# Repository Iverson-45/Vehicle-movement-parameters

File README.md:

Vehicle Movement Parameters Meter 
------

Authors: Jakub Litwin, Mateusz Prądziński, Adrian Andrószowski, Błażej Szkobel 
Overview

The goal of this project is to design and build a prototype device capable of measuring, calculating, and displaying real-time vehicle movement parameters. To ensure high data throughput, low latency, and a responsive UI, the system utilizes a Dual-MCU architecture that effectively splits the workload between sensor processing and data logging/display.
Calculated & Displayed Parameters:

    Speed: [km/h] 

    Acceleration: [m/s^2] (Instantaneous acceleration) 

    Power: [Hp] 

    Torque: [Nm] 

    Inclination: [°] (Pitch / Roll) 

Hardware Architecture

The device operates on two separate microcontrollers communicating via UART.

1. Main MCU (Data Processor)

    Microcontroller: STM32F411CEU6 

    Role: Handles all sensor data acquisition, scaling, filtration, and complex sensor fusion algorithms.

    Sensors: U-blox NEO-M8N (GPS) and BMI160 (IMU + Gyroscope).

2. Secondary MCU (Display & Logger)

    Microcontroller: STM32f303k8 

    Role: Receives processed numerical data from the Main MCU and handles the user interface.

    Peripherals: Drives a 2.0-inch TFT SPI Display and handles .csv data logging to a microSD card.

Firmware & Communication

    Main MCU: Programmed in low-level C (registers) to highly optimize the code for its specific tasks. It uses interrupt-driven peripherals to minimize delays and ensure smooth data reception. It synchronizes 100 data reads per second from the BMI160 and 5 reads per second from the GPS.

    Auxiliary MCU: Written in C utilizing the HAL library. It implements heavily optimized external libraries from GitHub for the ST7789 display and SPI SD card.

    Inter-MCU Communication: The two microcontrollers communicate via UART. At startup, they perform a handshake to initiate communication. The Aux MCU sends the user-defined vehicle mass to the Main MCU, and the Main MCU continuously streams back the calculated data.

How It Works: Algorithms & Calibration

To make the device user-friendly, it does not require perfectly leveled physical mounting inside the vehicle. Instead, the data passes through a complex algorithmic pipeline divided into three distinct phases:

Phase 1: Gravity Calibration While the vehicle is completely stationary, the device measures the Earth's gravitational pull to determine the gravity vector relative to the device's physical orientation. This establishes the true Z-axis (downward force).

Phase 2: Longitudinal Axis Calibration (Direction) The user performs a short, straight-line acceleration. The device detects this forward motion vector to define the X-axis (front). Using the cross product of these established forces, the software builds an orthonormal basis. This creates a 3D rotation matrix that mathematically rotates all raw sensor vectors to perfectly align with the vehicle's actual coordinate system, automatically compensating for any "crooked" mounting.

Phase 3: Active Operation During driving, raw data from the accelerometer and gyroscope is continuously transformed using the generated rotation matrix. The system calculates the device's tilt angles from the accelerometer and applies a Complementary Filter to fuse this data with the gyroscope readings for smooth, accurate inclination and acceleration outputs.
Current State & Future Development

Semester 1 Achievements:
A fully working prototype has been built that successfully handles instrument communication, calibration algorithms, the user interface, display presentation, and SD card .csv logging.

Next Steps (Semester 2 Goals): 

    Design a dedicated power supply section.

    Create a complete device schematic and custom PCB layout.

    Design a physical 3D enclosure/case.

    Conduct extensive real-world measurement tests.

    Develop PC software to visualize the saved telemetry data.

## Preliminary Measurement Results

During our initial field tests, the logged telemetry data was extracted and visualized using Python. We are pleased to report that the calculated power output closely aligns with the actual specifications of the vehicle used for testing.

**⚠️ Note:** Please keep in mind that this is an early prototype and not the final version of the system. The hardware architecture and calculation algorithms are still actively being refined. Further calibration, optimization, and extensive real-world validations are planned for the upcoming semester.

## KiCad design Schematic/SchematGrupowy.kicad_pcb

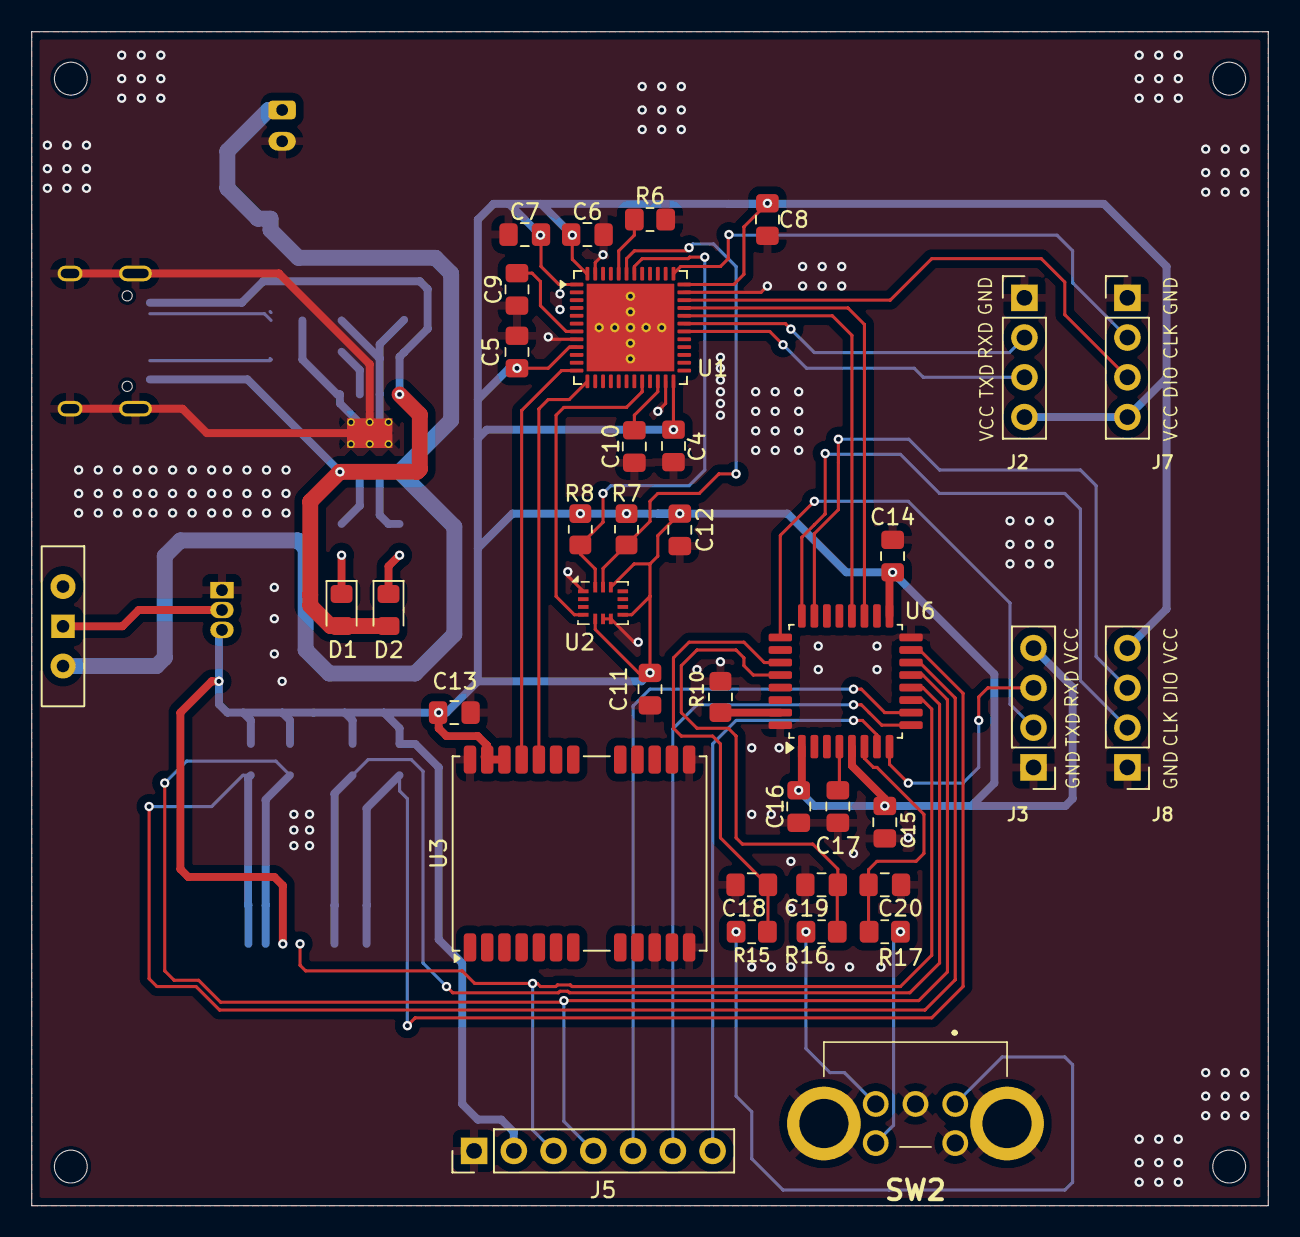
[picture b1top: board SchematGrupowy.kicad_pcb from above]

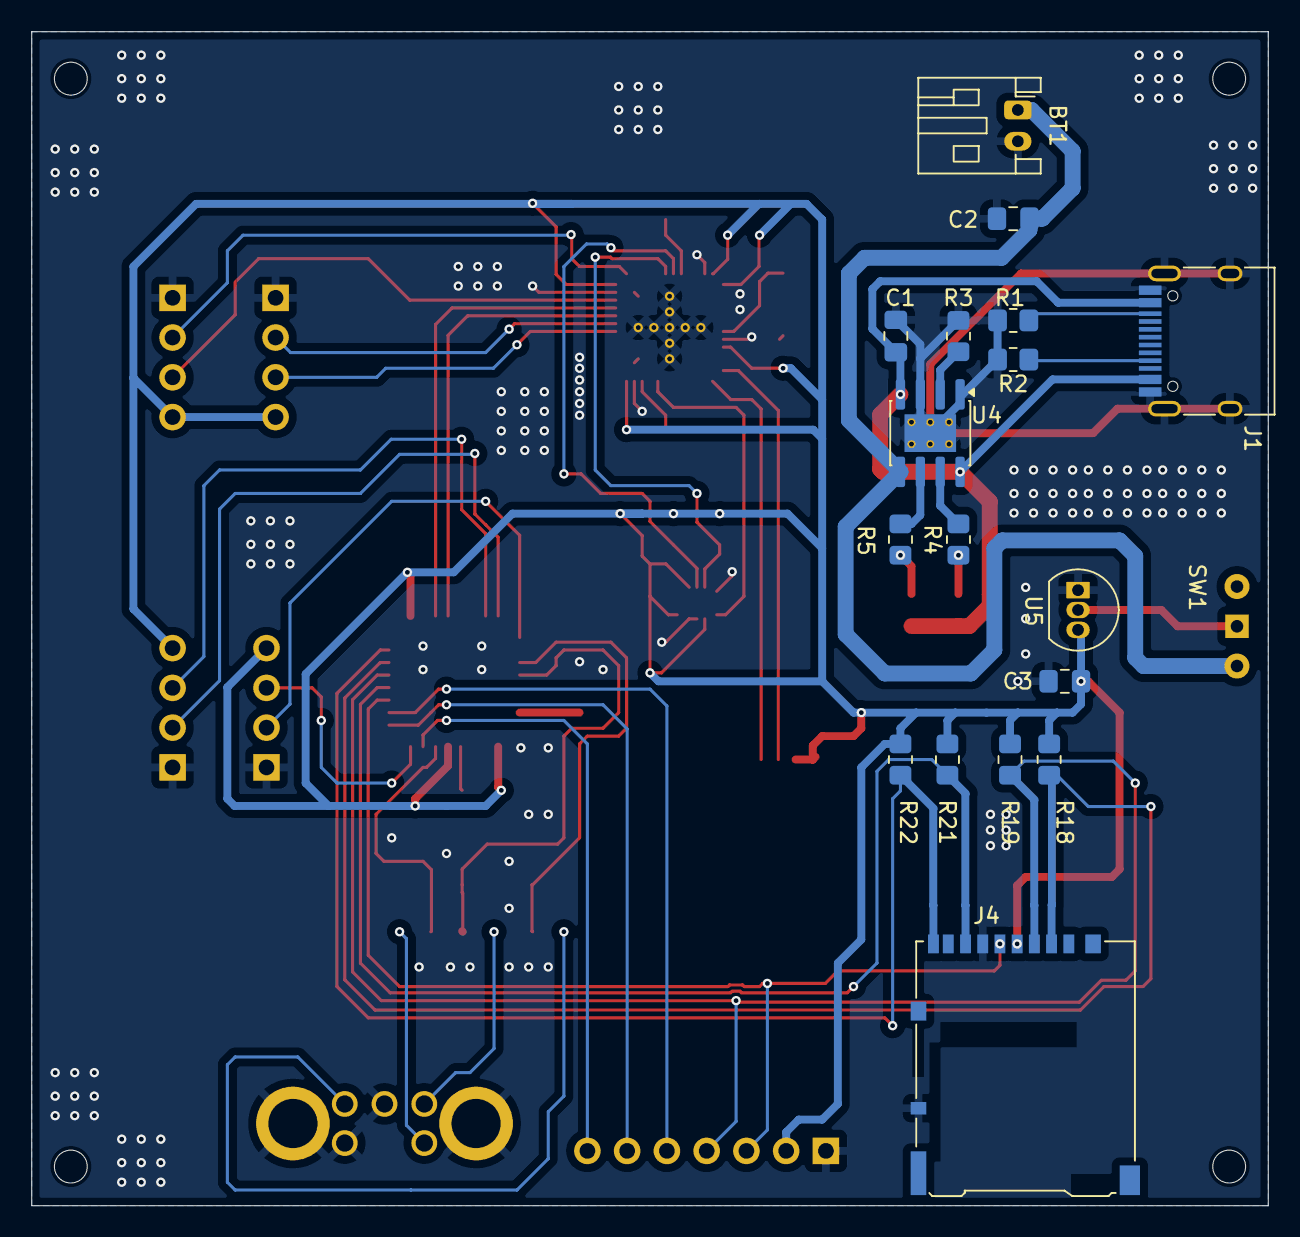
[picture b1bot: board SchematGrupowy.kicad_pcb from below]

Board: 2 copper layers, 79.0 x 75.0 mm, 54 parts (17 on the bottom side), 46 nets.

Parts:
BT1: Battery_Cell; JST_PH_S2B-PH-K_1x02_P2.00mm_Horizontal
C1, C2, C3: 10uF; C_0805_2012Metric_Pad1.18x1.45mm_HandSolder
C4: 4.7uF; C_0805_2012Metric_Pad1.18x1.45mm_HandSolder
C5, C6, C7, C8, C10, C11, C12, C13, C14, C15, C16: 100nF; C_0805_2012Metric_Pad1.18x1.45mm_HandSolder
C9, C17: 100n; C_0805_2012Metric_Pad1.18x1.45mm_HandSolder
C18, C19, C20: 10nF; C_0805_2012Metric_Pad1.18x1.45mm_HandSolder
D1, D2: LED; LED_0805_2012Metric_Pad1.15x1.40mm_HandSolder
J1: USB_C_Receptacle_USB2.0_14P; USB_C_Receptacle_HRO_TYPE-C-31-M-12
J2: UART1; PinHeader_1x04_P2.54mm_Vertical
J3: UART2; PinHeader_1x04_P2.54mm_Vertical
J4: Micro_SD_Card_Det1; microSD_HC_Hirose_DM3AT-SF-PEJM5
J5: LCD; PinHeader_1x07_P2.54mm_Vertical
J7: Programing1; PinHeader_1x04_P2.54mm_Vertical
J8: Programing2; PinHeader_1x04_P2.54mm_Vertical
R1, R2: 5.1k; R_0805_2012Metric_Pad1.20x1.40mm_HandSolder
R3: 1.1k; R_0805_2012Metric_Pad1.20x1.40mm_HandSolder
R4, R5: 1k; R_0805_2012Metric_Pad1.20x1.40mm_HandSolder
R6, R10, R15, R16, R17, R18, R19, R21, R22: 10k; R_0805_2012Metric_Pad1.20x1.40mm_HandSolder
R7, R8: 4.7k; R_0805_2012Metric_Pad1.20x1.40mm_HandSolder
SW1: SW_Wuerth_450301014042; SW_Slide-03_Wuerth-WS-SLTV_10x2.5x6.4_P2.54mm
SW2: RotaryEncoder_Switch_MP; EC11B15242AE
U1: STM32F411CEUx; QFN-48-1EP_7x7mm_P0.5mm_EP5.6x5.6mm
U2: BMI160; Bosch_LGA-14_3x2.5mm_P0.5mm
U3: NEO-M8N; ublox_NEO
U4: TP4056-42-ESOP8; SOIC-8-1EP_3.9x4.9mm_P1.27mm_EP2.41x3.3mm_ThermalVias
U5: MCP1700-3302E; TO-92_Inline
U6: STM32F303K8Tx; LQFP-32_7x7mm_P0.8mm

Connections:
+5V: C1.1, D1.2 (A), D2.2 (A), J1.A4 (VBUS), J1.A9 (VBUS), J1.B4 (VBUS), J1.B9 (VBUS), U4.4 (V_{CC}), U4.8 (CE)
BMI_INT1: U1.20 (PB2), U2.4 (INT1)
BMI_SCL: R8.2, U1.42 (PB6), U2.14 (SDx)
BMI_SDA: R7.2, U1.43 (PB7), U2.13 (SCx)
BTN_EA: C18.2, R15.1, U6.27 (PB4)
BTN_EB: C19.2, R16.2, U6.28 (PB5)
GND: BT1.2 (-), C1.2, C2.2, C3.2, C4.2, C5.2, C6.2, C7.2, C8.2, C9.2, C10.2, C11.2, C12.2, C13.2, C14.2, C15.2, C16.2, C17.2, C18.1, C19.1, C20.1, J1.A1 (GND), J1.A12 (GND), J1.B1 (GND), J1.B12 (GND), J1.S1 (SHIELD), J2.1, J3.1, J4.6 (VSS), J4.10 (SHIELD), J5.1, J7.1, J8.1, R1.2, R2.1, R3.2, R6.2, R10.2, SW2.C, SW2.MP, SW2.S2, U1.8 (VSSA), U1.23 (VSS), U1.35 (VSS), U1.47 (VSS), U1.49 (VSS), U2.1 (SDO), U2.6 (GNDIO), U2.7 (GND), U3.10 (GND), U3.12 (GND), U3.13 (GND), U3.24 (GND), U4.1 (TEMP), U4.3 (GND), U4.9 (EPAD), U5.1 (GND), U6.16 (VSS), U6.32 (VSS)
GPS_RXD: U1.12 (PA2), U3.21 (RXD/SPI_MOSI)
GPS_TXD: U1.13 (PA3), U3.20 (TXD/SPI_MISO)
MCU_CLK: J4.5 (CLK), J5.3, U6.11 (PA5)
MCU_MOSI: J4.3 (CMD), J5.4, R19.1, U6.13 (PA7)
MK12_RXDTXD: U1.33 (PA12), U6.19 (PA9)
MK12_TXDRXD: U1.32 (PA11), U6.20 (PA10)
unnamed: BT1.1 (+), C2.1, SW1.3 (A), U4.5 (BAT)
unnamed: D1.1 (K), R4.1
unnamed: D2.1 (K), R5.1
unnamed: J1.A5 (CC1), R2.2
unnamed: J1.B5 (CC2), R1.1
unnamed: R15.2, SW2.A
unnamed: R16.1, SW2.B
unnamed: R17.1, SW2.S1
unnamed: SW1.1 (B), U5.2 (VI)
unnamed: R6.1, U1.44 (BOOT0)
unnamed: C9.1, U1.7 (NRST)
unnamed: C4.1, U1.22 (VCAP1)
unnamed: R3.1, U4.2 (PROG)
unnamed: R4.2, U4.7 (~CHRG)
unnamed: R5.2, U4.6 (~STDBY)
unnamed: R10.1, U6.31 (BOOT0)
unnamed: C17.1, U6.4 (NRST)
SD_CS: J4.2 (DAT3/CD), R18.1, U6.14 (PB0)
SD_DET: J4.9 (DET), R22.1, U6.15 (PB1)
SD_MISO: J4.7 (DAT0), R21.1, U6.12 (PA6)
SW1: C20.2, R17.2, U6.6 (PA0)
SWCLK_1: J7.2, U1.37 (PA14)
SWCLK_2: J8.2, U6.24 (PA14)
SWDIO_1: J7.3, U1.34 (PA13)
SWDIO_2: J8.3, U6.23 (PA13)
TFT_CS: J5.7, U6.7 (PA1)
TFT_DC: J5.6, U6.9 (PA3)
TFT_RST: J5.5, U6.10 (PA4)
UART2_RXD: J3.3, U6.8 (PA2)
UART2_TXD: J3.2, U6.25 (PA15)
UART_RXD: J2.2, U1.31 (PA10)
UART_TXD: J2.3, U1.30 (PA9)
VCC: C3.1, C5.1, C6.1, C7.1, C8.1, C10.1, C11.1, C12.1, C13.1, C14.1, C15.1, C16.1, J2.4, J3.4, J4.4 (VDD), J5.2, J7.4, J8.4, R7.1, R8.1, R18.2, R19.2, R21.2, R22.2, U1.1 (VBAT), U1.9 (VDDA), U1.24 (VDD), U1.36 (VDD), U1.48 (VDD), U2.5 (VDDIO), U2.8 (VDD), U2.12 (CSB), U3.22 (V_BCKP), U3.23 (VCC), U5.3 (VO), U6.1 (VDD), U6.5 (VDDA), U6.17 (VDD)

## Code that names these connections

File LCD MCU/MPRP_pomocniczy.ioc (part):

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Mcu.Name=STM32F303K(6-8)Tx
Mcu.Package=LQFP32
Mcu.UserName=STM32F303K8Tx
PA0.GPIOParameters=GPIO_PuPd,GPIO_Label
PA0.GPIO_Label=ENC_BTN
PA0.GPIO_PuPd=GPIO_PULLUP
PA0.Signal=GPIO_Input
PA1.GPIOParameters=GPIO_Speed,GPIO_Label
PA1.GPIO_Label=TFT_CS
PA1.GPIO_Speed=GPIO_SPEED_FREQ_HIGH
PA1.Signal=GPIO_Output
PA10.GPIOParameters=GPIO_Label
PA10.GPIO_Label=UART_RX
PA10.Mode=Asynchronous
PA10.Signal=USART1_RX
PA13.GPIOParameters=GPIO_Label
PA13.GPIO_Label=SWDIO
PA13.Signal=SYS_JTMS-SWDIO
PA14.GPIOParameters=GPIO_Label
PA14.GPIO_Label=SWCLK
PA14.Signal=SYS_JTCK-SWCLK
PA15.GPIOParameters=GPIO_Label
PA15.GPIO_Label=VCP_RX
PA15.Mode=Asynchronous
PA15.Signal=USART2_RX
PA2.GPIOParameters=GPIO_Label
PA2.GPIO_Label=VCP_TX
PA2.Mode=Asynchronous
PA2.Signal=USART2_TX
PA3.GPIOParameters=GPIO_Speed,GPIO_Label
PA3.GPIO_Label=TFT_DC
PA3.GPIO_Speed=GPIO_SPEED_FREQ_LOW
PA3.Signal=GPIO_Output
PA4.GPIOParameters=GPIO_Speed,GPIO_Label
PA4.GPIO_Label=TFT_RST
PA4.GPIO_Speed=GPIO_SPEED_FREQ_LOW
PA4.Signal=GPIO_Output
PA5.Mode=Full_Duplex_Master
PA5.Signal=SPI1_SCK
PA6.Mode=Full_Duplex_Master
PA6.Signal=SPI1_MISO
PA7.Mode=Full_Duplex_Master
PA7.Signal=SPI1_MOSI
PA9.GPIOParameters=GPIO_Label
PA9.GPIO_Label=UART_TX
PA9.Mode=Asynchronous
PA9.Signal=USART1_TX
PB0.GPIOParameters=GPIO_Speed,GPIO_Label
PB0.GPIO_Label=SD_CS
PB0.GPIO_Speed=GPIO_SPEED_FREQ_HIGH
PB0.Signal=GPIO_Output
PB1.GPIOParameters=GPIO_PuPd,GPIO_Label
PB1.GPIO_Label=SD_DETECT
PB1.GPIO_PuPd=GPIO_PULLUP
PB1.Signal=GPIO_Input
PB4.Signal=S_TIM3_CH1
PB5.Signal=S_TIM3_CH2
PF0\ /\ OSC_IN.GPIOParameters=GPIO_Label
PF0\ /\ OSC_IN.GPIO_Label=MCO
PF0\ /\ OSC_IN.Signal=RCC_OSC_IN
RCC.HSEPLLFreq_Value=8000000
RCC.HSE_VALUE=8000000
RCC.SYSCLKFreq_VALUE=64000000
RCC.SYSCLKSourceVirtual=RCC_SYSCLKSOURCE_PLLCLK
board=NUCLEO-F303K8
boardIOC=true

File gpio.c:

#include "gpio.h"

void I2cPins(void)
{
    // B6 - SCL, B7 - SDA
    RCC->AHB1ENR |= RCC_AHB1ENR_GPIOBEN;

    // Alternate function (10)
    GPIOB->MODER &= ~(GPIO_MODER_MODER6 | GPIO_MODER_MODER7);
    GPIOB->MODER |= (GPIO_MODER_MODER6_1 | GPIO_MODER_MODER7_1);

    // Open-drain (1)
    GPIOB->OTYPER |= (GPIO_OTYPER_OT_6 | GPIO_OTYPER_OT_7);

    // High speed (10) lub Very High speed (11)
    GPIOB->OSPEEDR |= (GPIO_OSPEEDR_OSPEED6_1 | GPIO_OSPEEDR_OSPEED7_1);


    // Pull-up (01)
    GPIOB->PUPDR &= ~(GPIO_PUPDR_PUPDR6 | GPIO_PUPDR_PUPDR7);
    GPIOB->PUPDR |= (GPIO_PUPDR_PUPDR6_0 | GPIO_PUPDR_PUPDR7_0);

    // AF4 = I2C1 B6 i B7
    GPIOB->AFR[0] &= ~(GPIO_AFRL_AFSEL6 | GPIO_AFRL_AFSEL7);
    GPIOB->AFR[0] |= (4 << GPIO_AFRL_AFSEL6_Pos) | (4 << GPIO_AFRL_AFSEL7_Pos);
}

void Uart2Pins(void)
{
	// PA2 - TX, PA3 - RX
    RCC->AHB1ENR |= RCC_AHB1ENR_GPIOAEN;

    GPIOA->MODER &= ~(GPIO_MODER_MODER2 | GPIO_MODER_MODER3);
    GPIOA->MODER |= (GPIO_MODER_MODER2_1 | GPIO_MODER_MODER3_1);

    GPIOA->OSPEEDR |= (GPIO_OSPEEDR_OSPEED2_1 | GPIO_OSPEEDR_OSPEED3_1);

    // PA2 no-pull, PA3 pull-up
    GPIOA->PUPDR &= ~(GPIO_PUPDR_PUPDR2 | GPIO_PUPDR_PUPDR3);
    GPIOA->PUPDR |= GPIO_PUPDR_PUPDR3_0;

    // AF7 = USART2
    GPIOA->AFR[0] &= ~(GPIO_AFRL_AFSEL2 | GPIO_AFRL_AFSEL3);
    GPIOA->AFR[0] |= (7 << GPIO_AFRL_AFSEL2_Pos) | (7 << GPIO_AFRL_AFSEL3_Pos);
}

void Uart1Pins(void)
{
    // PA9 (TX), PA10 (RX)
    RCC->AHB1ENR |= RCC_AHB1ENR_GPIOAEN;

    // --- PA9 (TX) ---
    GPIOA->MODER &= ~GPIO_MODER_MODER9;
    GPIOA->MODER |= GPIO_MODER_MODER9_1; // AF

    GPIOA->OSPEEDR |= GPIO_OSPEEDR_OSPEED9_1; // High Speed

    // AF7  USART1  PA9
    GPIOA->AFR[1] &= ~GPIO_AFRH_AFSEL9;
    GPIOA->AFR[1] |= (7 << GPIO_AFRH_AFSEL9_Pos);

    // --- PA10 (RX) ---
    GPIOA->MODER &= ~GPIO_MODER_MODER10;
    GPIOA->MODER |= GPIO_MODER_MODER10_1; // AF

    GPIOA->PUPDR &= ~GPIO_PUPDR_PUPDR10;
    GPIOA->PUPDR |= GPIO_PUPDR_PUPDR10_0; // Pull-up

    // AF7  USART1  PA10
    GPIOA->AFR[1] &= ~GPIO_AFRH_AFSEL10;
    GPIOA->AFR[1] |= (7 << GPIO_AFRH_AFSEL10_Pos);
}

void Uart6Pins(void)
{
	// PA11 - TX, PA12 - RX
    RCC->AHB1ENR |= RCC_AHB1ENR_GPIOAEN;

    GPIOA->MODER &= ~(GPIO_MODER_MODER11 | GPIO_MODER_MODER12);
    GPIOA->MODER |= (GPIO_MODER_MODER11_1 | GPIO_MODER_MODER12_1);

    // AF8  USART6
    GPIOA->AFR[1] &= ~(GPIO_AFRH_AFSEL11 | GPIO_AFRH_AFSEL12);
    GPIOA->AFR[1] |= (8 << GPIO_AFRH_AFSEL11_Pos) | (8 << GPIO_AFRH_AFSEL12_Pos);
}

void Init_GPIO_Interrupt(void)
{
	// PB2 external interrupt
    RCC->AHB1ENR |= RCC_AHB1ENR_GPIOBEN;
    RCC->APB2ENR |= RCC_APB2ENR_SYSCFGEN;

    // PB2 input
    GPIOB->MODER &= ~(GPIO_MODER_MODER2);

    // PB2 pull-down
    GPIOB->PUPDR &= ~(GPIO_PUPDR_PUPDR2);
    GPIOB->PUPDR |= GPIO_PUPDR_PUPDR2_1;

    // Connect EXTI2 to PB2
    SYSCFG->EXTICR[0] &= ~(SYSCFG_EXTICR1_EXTI2);
    SYSCFG->EXTICR[0] |= SYSCFG_EXTICR1_EXTI2_PB;

    // EXTI Configuration
    EXTI->IMR |= EXTI_IMR_MR2;
    EXTI->RTSR |= EXTI_RTSR_TR2; // Rising edge
    EXTI->PR |= EXTI_PR_PR2;     // Clear pending flag

    // NVIC  EXTI2
    NVIC_SetPriority(EXTI2_IRQn, 2);
    NVIC_EnableIRQ(EXTI2_IRQn);
}

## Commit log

2025-11-24 Update README with system and hardware details
    Added system description and hardware specifications.
2025-11-25 Update display information in README
2025-11-25 Updated main
    Added velocity updating on LCD and UART-PC debuging
2025-11-25 Refactor main.h to include new headers
2025-11-25 moved uart1.c & uart2.c functions to uart.c
2025-11-25 Moved uart1.h & uart2.h to uart.h
2025-11-25 Update and rename ubx.c to gps.c
    GPS functions from uart1.c are moved to gps.c
2025-11-25 Added lcd library
2025-11-25 Added lcd library header
2025-11-25 Update README
    Added a section for stages in README.
2025-11-25 Add image for display speed in README
2025-11-25 Implement function for display orientation
    Added ST7567_SetRotation function to set display orientation.
2025-11-25 Add ST7567_SetRotation function prototype
2025-11-25 Add BMI160 header file
2025-11-25 Add BMI160 sensor driver implementation
    This file implements functions to read and write data from the BMI160 sensor, initialize it, and read accelerometer and gyroscope data.
2025-11-25 Add 5x7 font bitmap for lcd
2025-11-26 Fixed LCD refreshing
2025-11-26 Remove unused variable and clean up gps.h
2025-11-26 Updated header file
2025-11-26 Added interrupts for imu readings
2025-11-26 Implement GPIO interrupt initialization for PA1
    Added GPIO initialization for external interrupt on PA1.
2025-11-26 Add Init_GPIO_Interrupt function declaration
2025-11-26 Refactor main initialization and add bmi160 reading
2025-11-26 Add i2c and clock config
2025-11-28 Refactor GPS data handling and parsing logic
2025-11-28 Update gps.h with new variables and function
    Added buffer and gps_ready_flag variables, and a new function ParseSpeed.
2025-11-28 Update main
    Added GPS speed logging functionality to UART output.
2025-11-28 Update clock
2025-12-14 Changed main MCU & added support for communication with secondary MCU for display output
2025-12-15 Added degrees algorythm
2025-12-15 inclination relative to the device start position
2025-12-25 Added second MCU code & fixed bugs
2026-01-06 Refactor main.c for LCD
    Updated the main program for LCD receiver to improve functionality and added averaging for telemetry data.
2026-01-06 Implement USART6 IRQ and refine acceleration logic
    Added USART6 interrupt handler and adjusted acceleration calculation.
2026-01-09 Added encoder, sd card support. Created UI.
2026-03-04 Update microcontroller model and communication details
    Updated microcontroller model and clarified communication description.
2026-03-10 Revise README for clarity and additional information
    Updated README to enhance project overview and details.
2026-03-10 Refactor main.c for filter implementation
    Fixed problems with fusion filter. Added adaptive filter.
2026-03-10 Python script for drawing chart
2026-03-11 Added schematic
2026-03-13 Apply final touches to PCB design
2026-03-14 Resolve DRC issues and pour ground planes
2026-03-17 Added descriptions for programming/uart pins
2026-03-18 Added Gerbres,screens and footprint fixes
2026-05-20 Refreshed files
